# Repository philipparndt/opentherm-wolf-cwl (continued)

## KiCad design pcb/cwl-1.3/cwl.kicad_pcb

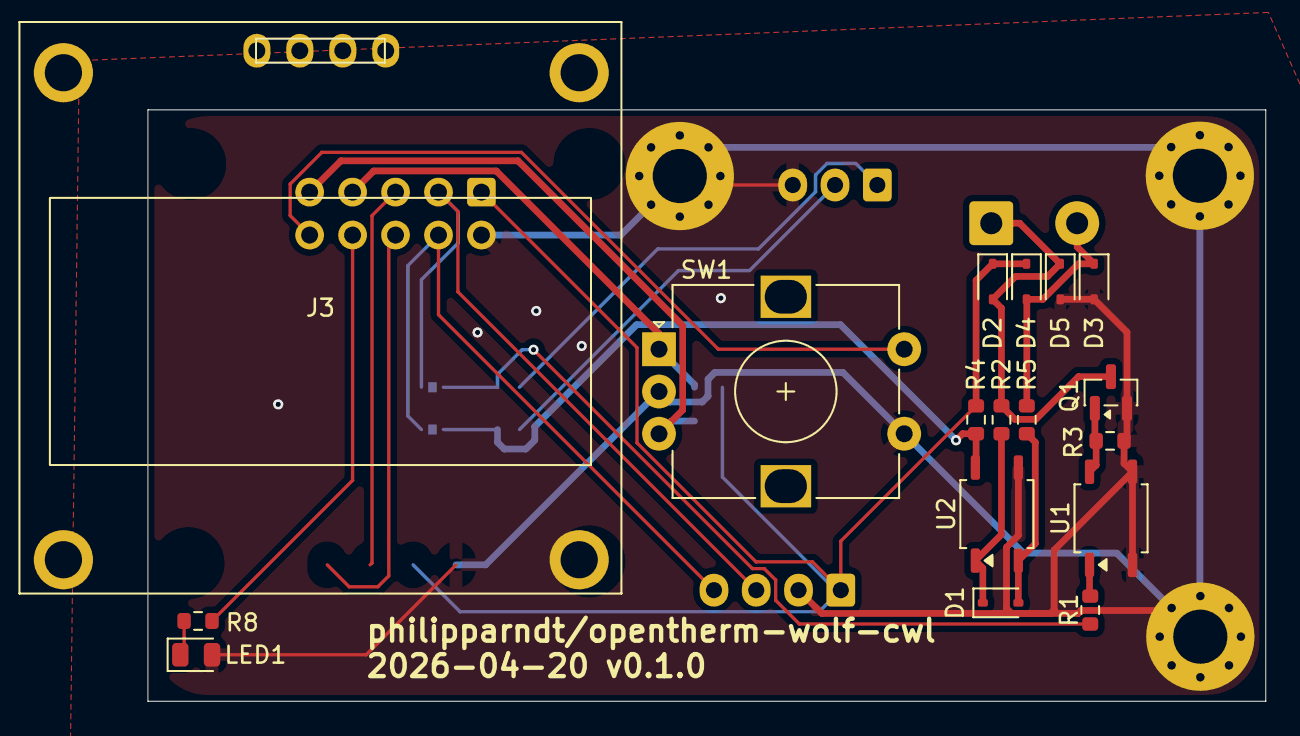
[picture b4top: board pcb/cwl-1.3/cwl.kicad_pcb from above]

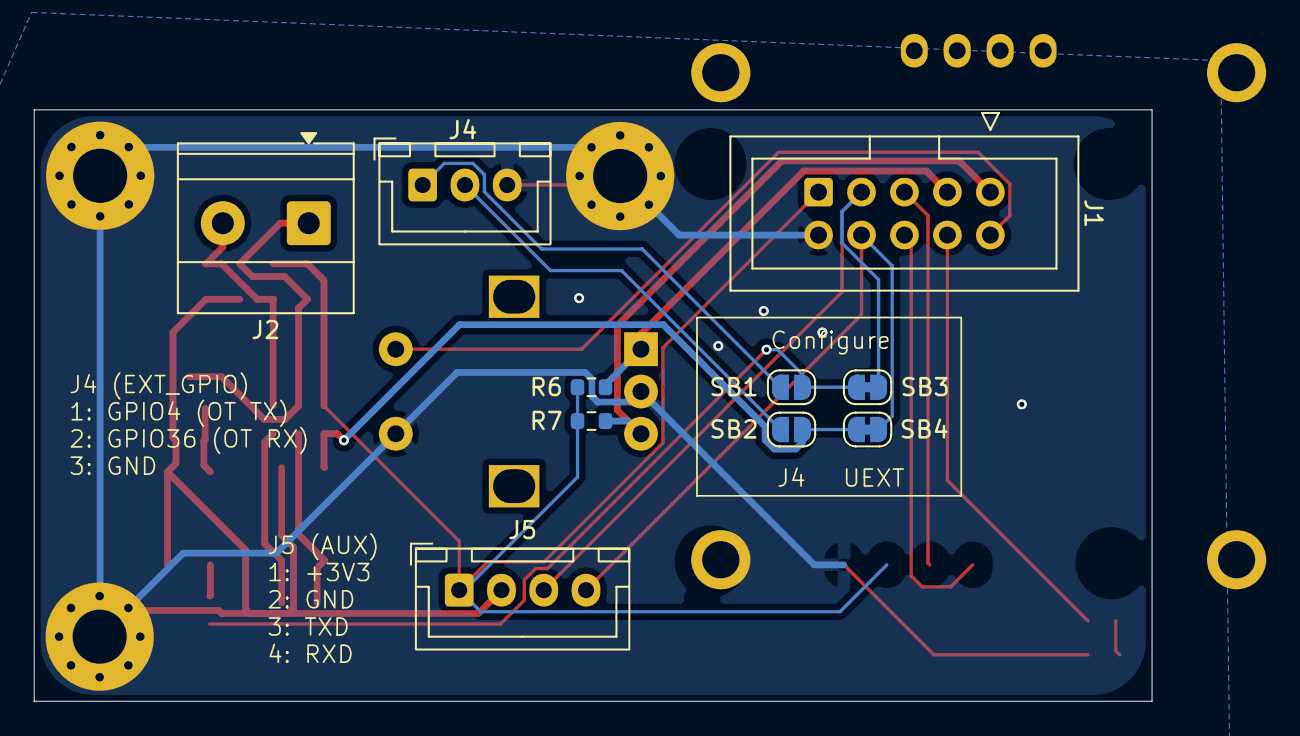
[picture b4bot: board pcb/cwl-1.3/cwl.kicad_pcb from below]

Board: 2 copper layers, 66.1 x 35.0 mm, 30 parts (10 on the bottom side), 21 nets.

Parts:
D1: BZX384-C4V7; D_SOD-323
D2, D3, D4, D5: 1N4148WS; D_SOD-323
J1: UEXT; IDC-Stecker_2x05_P2.54mm_Vertical
J2: OpenTherm; TerminalBlock_Phoenix_MKDS-1,5-2-5.08_1x02_P5.08mm_Horizont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
J3: OLED_SH1106_1.3; 128x64OLED-MountingHoles-Large
J4: EXT_GPIO; JST_XH_B3B-XH-A_1x03_P2.50mm_Vertical
J5: AUX; JST_XH_B4B-XH-A_1x04_P2.50mm_Vertical
LED1: Green; LED_0805_2012Metric
MH1, MH2, MH4: M3; MountingHole_3.2mm_M3_Pad_Via
Q1: 2N7002; SOT-23
R1: 330; R_0603_1608Metric
R2: 680; R_0603_1608Metric
R3: 4.7k; R_0603_1608Metric
R4, R6, R7: 10k; R_0603_1608Metric
R5, R8: 1k; R_0603_1608Metric
SB1: GPIO4→OT_TX; SolderJumper-2_P1.3mm_Open_RoundedPad1.0x1.5mm
SB2: GPIO36→OT_RX; SolderJumper-2_P1.3mm_Open_RoundedPad1.0x1.5mm
SB3: TXD→OT_TX; SolderJumper-2_P1.3mm_Bridged_RoundedPad1.0x1.5mm
SB4: RXD→OT_RX; SolderJumper-2_P1.3mm_Bridged_RoundedPad1.0x1.5mm
SW1: EC12E24204A9; RotaryEncoder_Alps_EC12E-Switch_Vertical_H20mm
U1, U2: LTV-817S-B; SOP-4_3.8x4.1mm_P2.54mm

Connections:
+3V3: D2.1, D4.1, J1.1, J3.1, J5.1, R4.2, R6.2, R7.2
ENC_CLK: J1.7, R6.1, SW1.A
ENC_DT: J1.9, R7.1, SW1.B
ENC_SW: J1.10, SW1.S1
GND: D3.2, D5.2, J1.2, J3.2, J4.3, J5.2, LED1.2, MH1.1, MH2.1, MH4.1, Q1.2, R3.2, SW1.C, SW1.S2, U1.2, U1.3, U2.3
GPIO4: J4.1, SB1.1
GPIO36: J4.2, SB2.1
LED_ANODE: LED1.1, R8.2
LED_GPIO: J1.8, R8.1
OT+: D2.2, D5.1, J2.1, Q1.3, R2.1
OT-: D3.1, D4.2, J2.2, R5.2
OT_RX_SIG: R4.1, SB2.2, SB4.2, U2.4
OT_TX_SIG: R1.1, SB1.2, SB3.2
RX_ANODE: D1.1, R2.2, U2.1
RX_CATHODE: D1.2, R5.1, U2.2
SCL: J1.5, J3.3
SDA: J1.6, J3.4
TX_GATE: Q1.1, R3.1, U1.4
TX_LED: R1.2, U1.1
UEXT_RXD: J1.4, J5.4, SB4.1
UEXT_TXD: J1.3, J5.3, SB3.1

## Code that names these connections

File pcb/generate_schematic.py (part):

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enc_clk = Net("ENC_CLK")
enc_dt = Net("ENC_DT")
enc_sw = Net("ENC_SW")
led_gpio = Net("LED_GPIO")
ot_tx_sig = Net("OT_TX_SIG")   # internal OT TX signal (goes to R1)
ot_rx_sig = Net("OT_RX_SIG")   # internal OT RX signal (goes to R4/U2)
ot_plus = Net("OT+")
ot_minus = Net("OT-")

# GPIO nets from connectors
gpio4 = Net("GPIO4")
gpio36 = Net("GPIO36")
uext_txd = Net("UEXT_TXD")
uext_rxd = Net("UEXT_RXD")

# =============================================================================
# J4: EXT Header — GPIO4 + GPIO36 from ESP32-POE EXT1/EXT2
# Omitted on cwl-diyless: the DIYless shield doesn't expose these GPIOs.
# =============================================================================
if VARIANT != "cwl-diyless":
    j4 = make_connector("J4", "EXT_GPIO", 3, "Connector_JST:JST_XH_B3B-XH-A_1x03_P2.50mm_Vertical")

    j4["P1"] += gpio4
    j4["P2"] += gpio36
    j4["P3"] += gnd

# =============================================================================
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j1["P5"] += scl
j1["P6"] += sda
j1["P7"] += enc_clk
j1["P8"] += led_gpio
j1["P9"] += enc_dt
j1["P10"] += enc_sw

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# UEXT TXD/RXD via J6/J7 below, no bridges needed.
# =============================================================================
if VARIANT != "cwl-diyless":
    sb1 = SOLDER_BRIDGE_OPEN("SB1", "GPIO4→OT_TX")
    sb2 = SOLDER_BRIDGE_OPEN("SB2", "GPIO36→OT_RX")
    sb3 = SOLDER_BRIDGE_CLOSED("SB3", "TXD→OT_TX")
    sb4 = SOLDER_BRIDGE_CLOSED("SB4", "RXD→OT_RX")

    # SB1: GPIO4 (J4) → OT TX signal (default: open)
    gpio4 += sb1["1"]
    sb1["2"] += ot_tx_sig

    # SB2: GPIO36 (J4) → OT RX signal (default: open)
    gpio36 += sb2["1"]
    sb2["2"] += ot_rx_sig

    # SB3: UEXT TXD → OT TX signal (default: closed)
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    sb4["2"] += ot_rx_sig
else:
    # cwl-diyless: wire UEXT TXD/RXD straight through to the shield's pin
    # headers (J6/J7 below). No solder bridges, no GPIO4/GPIO36 routing.
    ot_tx_sig += uext_txd
    ot_rx_sig += uext_rxd

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
    j5["P1"] += vcc             # +3V3
    j5["P2"] += gnd             # GND
    j5["P3"] += uext_txd        # TXD (GPIO1)
    j5["P4"] += uext_rxd        # RXD (GPIO3)

# =============================================================================
# J2: Screw Terminal — OpenTherm bus (cwl/cwl-1.3 only)
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    q1["D"] += ot_plus
    q1["S"] += gnd

    # RX: OT+ → R2 → U2 (opto) → GPIO36
    r2 = R("R2", "680")
    r4 = R("R4", "10k")
    r5 = R("R5", "1k")
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#   Left column  (pins 1..8, top→bottom):
#     1=RST, 2=A0, 3=D0, 4=D5, 5=D6, 6=D7, 7=D8, 8=3V3
#   Right column (pins 9..16, top→bottom):
#     9=TX, 10=RX, 11=D1 (GPIO5), 12=D2 (GPIO4),
#     13=D3, 14=D4, 15=GND, 16=5V
#
# Only 4 of 16 pins are wired (3V3, D1, D2, GND); the rest are NC pads that
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if VARIANT == "cwl-diyless":
    j6 = make_connector("J6", "D1mini", 16, "D1mini:D1_Mini_2x08_P2.54mm")
    j6["P8"]  += vcc       # 3V3
    j6["P11"] += ot_tx_sig # D1 (GPIO 5) — MCU → shield → OT bus
    j6["P12"] += ot_rx_sig # D2 (GPIO 4) — OT bus → shield → MCU
    j6["P15"] += gnd       # GND

# =============================================================================
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    j8["P5"] += scl
    j8["P6"] += sda
    j8["P7"] += enc_clk
    j8["P8"] += led_gpio
    j8["P9"] += enc_dt
    j8["P10"] += enc_sw

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led1 = LED("LED1", "Green")

led_anode = Net("LED_ANODE")
led_gpio += r8["1"]
r8["2"] += led_anode
led_anode += led1["A"]
led1["K"] += gnd
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
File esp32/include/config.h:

/**
 * Configuration for Wolf CWL OpenTherm Controller
 *
 * Controls a Wolf CWL 300 ventilation unit via OpenTherm protocol
 * using a DIYLess Master OpenTherm Shield.
 *
 * FIRST TIME SETUP:
 * 1. Build and flash the firmware
 * 2. Device starts in AP mode: connect to "WolfCWL-XXXX" WiFi
 * 3. Configure WiFi and MQTT settings via web UI
 * 4. Device restarts and connects to your network
 * 5. Access web UI at http://wolf-cwl.local
 */

#ifndef CONFIG_H
#define CONFIG_H

// =============================================================================
// WiFi Settings
// =============================================================================
// Leave empty for AP mode setup via web UI
// #define WIFI_SSID           ""
// #define WIFI_PASSWORD       ""

// =============================================================================
// MQTT Settings
// =============================================================================
// Configure via web UI
// #define MQTT_SERVER         ""
// #define MQTT_PORT           1883
// #define MQTT_USERNAME       ""
// #define MQTT_PASSWORD       ""
// #define MQTT_TOPIC          "wolf-cwl"

// =============================================================================
// OpenTherm Pin Configuration (DIYLess Thermostat Shield)
// =============================================================================
// Default pins for DIYLess shield, override in platformio.ini if needed
// #define PIN_OT_IN           21
// #define PIN_OT_OUT          22

// =============================================================================
// OLED Display (SH1106 128x64 I2C)
// =============================================================================
// #define PIN_SDA             19
// #define PIN_SCL             23

// =============================================================================
// Rotary Encoder (KY-040)
// =============================================================================
// #define PIN_ENC_CLK         16
// #define PIN_ENC_DT          17
// #define PIN_ENC_SW          5

#endif // CONFIG_H

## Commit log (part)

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2026-04-25 initial version
2026-04-25 ignore file
2026-04-25 initial analysis
2026-04-25 update docs
2026-04-25 Add TSP register decoding for ventilation units
2026-04-25 first draft of the firmware
2026-04-25 ota updates
2026-04-27 archived specs
2026-04-27 feat: show network state changes
2026-04-28 feat: improve mode switching
2026-04-30 gitignore
2026-04-30 update display
2026-05-01 i18n
2026-05-01 chore: remove c++ firmware
2026-05-01 chore: archive completed openspec change
2026-05-01 generate gerber files
2026-05-01 clean up
2026-05-01 add printable idc connector
2026-05-01 feat: display rotation
2026-05-09 Add renovate.json
2026-05-13 chore: archive completed changes, add cwl-1.3 PCB variant
    - Archive completed OpenSpec changes under 2026-05-01:
    bypass-default, timed-off-cancel, home-header-mode,
    pending-mode-indicator, main-screen-schedule-indicator,
    rust-rewrite, ventilation-select-schedule-return
    - Add new cwl-1.3 PCB variant with KiCad project files
    - Add OLED SH1106 0.96" 3D model and large mounting-hole
2026-05-13 add partitions
2026-05-14 feat: support baked in wifi setup
2026-05-15 diyless variant
2026-05-17 manual schematic
2026-05-17 new pcb
2026-05-17 mouser parts
2026-05-23 fix: connection stability
    Filter detection via OEM LO bit, off-timer overhaul
    CWL filter signal:
    - Decode filter status from Status ID 70 LO byte bit 5 (Wolf/Brink/
    Viessmann OEM extension), confirmed in FIL_CLEAN.sal — the spec
    HI bit 4 is never set on this hardware and the HI fault bit is
    permanently latched, so neither is usable as a service signal.
2026-05-23 add 3d case
2026-05-23 feat: rust ot driver
2026-05-23 fix: ot rust driver
2026-05-23 Squashed commit of the following:
    commit 481deb4d1ac36ea8330ec88192de51c7a3cb352c
    Author: Philipp Arndt <2f.mail@gmx.de>
    Date: Sat May 23 19:26:29 2026 +0200
    fix: ot rust driver
    commit bb2b8b5b12621ffa75fe9bfb667a38aa0396d298
    Author: Philipp Arndt <2f.mail@gmx.de>
2026-05-25 update pcbs
2026-06-14 Bump esbuild and vite in /esp32/web
    Removes [esbuild](https://github.com/evanw/esbuild). It's no longer used after updating ancestor dependency [vite](https://github.com/vitejs/vite/tree/HEAD/packages/vite). These dependencies need to 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
    Removes `esbuild`
    Updates `vite` from 6.4.2 to 8.0.16
    - [Release notes](https://github.com/vitejs/vite/releases)
    - [Changelog](https://github.com/vitejs/vite/blob/main/packages/vite/CHANGELOG.md)
    - [Commits](https://github.com/vitejs/vite/commits/v8.0.16/packages/vite)
2026-06-20 Bump undici from 7.25.0 to 7.28.0 in /esp32/web
    Bumps [undici](https://github.com/nodejs/undici) from 7.25.0 to 7.28.0.
    - [Release notes](https://github.com/nodejs/undici/releases)
    - [Commits](https://github.com/nodejs/undici/compare/v7.25.0...v7.28.0)
    ---
    updated-dependencies:
    - dependency-name: undici
2026-06-25 history page + tz
2026-06-25 feat: extreme heat mode
2026-06-25 feat: extreme heat humidity handling
2026-06-25 chore: clean up temperatures
2026-06-26 feat: timeline chart improvements
2026-06-27 feat: actual vent level, boot-safe climate state, MQTT docs
    Show the unit's actual running level (derived from relative
    ventilation ID 77) instead of the commanded level (ID 71), since
    the two can differ. The status display and pending-spinner clear
    now track actualLevel; exposed as ventilation.actualLevel on
    /api/status via the new VentLevel::from_relative_pct (also reused
    for initial-level inference in ot_master).
2026-06-27 case (interm)
2026-06-27 feat: add sensor plausibility check
2026-06-27 case
2026-06-27 slim variant
2026-06-30 chore(deps-dev): bump vite from 6.4.2 to 8.1.0 in /esp32/web
    Bumps [vite](https://github.com/vitejs/vite/tree/HEAD/packages/vite) from 6.4.2 to 8.1.0.
    - [Release notes](https://github.com/vitejs/vite/releases)
    - [Changelog](https://github.com/vitejs/vite/blob/main/packages/vite/CHANGELOG.md)
    - [Commits](https://github.com/vitejs/vite/commits/create-vite@8.1.0/packages/vite)
    ---
    updated-dependencies:
